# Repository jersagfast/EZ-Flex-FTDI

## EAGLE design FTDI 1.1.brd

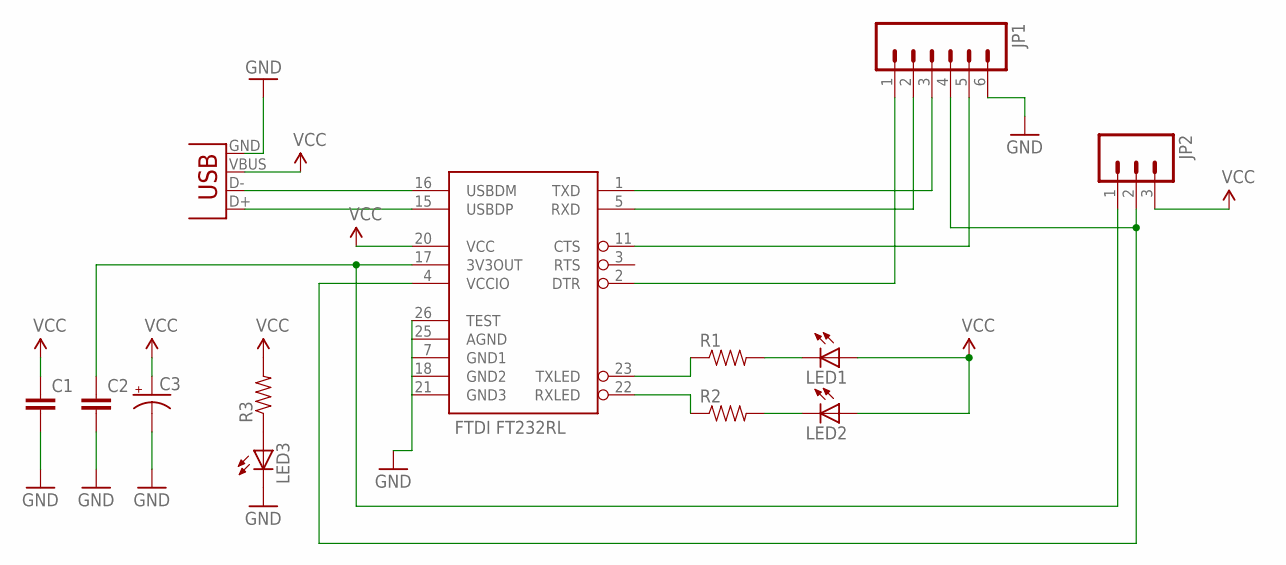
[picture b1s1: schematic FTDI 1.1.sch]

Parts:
C1, C2: CAP0603-CAP; 0603-CAP
C3: CAP_POL1206; EIA3216
JP1: M06SIP; 1X06
JP2: M03PTH; 1X03
LED1, LED2, LED3: LED0603; LED-0603
R1, R2, R3: RESISTOR0603-RES; 0603-RES
U1: FT232RL-BASICSSOP; SSOP28DB
X1: USB-SMD-NS; USB-MINIB-NOSTOP

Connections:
GND: C1.2, C2.2, C3.C (-), JP1.6, LED3.C, U1.7 (GND1), U1.18 (GND2), U1.21 (GND3), U1.25 (AGND), U1.26 (TEST), X1.GND
unnamed: U1.16 (USBDM), X1.D-
unnamed: R1.1, U1.23 (TXLED)
unnamed: LED1.C, R1.2
unnamed: LED2.C, R2.2
unnamed: R2.1, U1.22 (RXLED)
unnamed: U1.15 (USBDP), X1.D+
unnamed: JP1.1, U1.2 (DTR)
unnamed: JP1.2, U1.5 (RXD)
unnamed: JP1.3, U1.1 (TXD)
unnamed: JP1.5, U1.11 (CTS)
unnamed: JP1.4, JP2.2, U1.4 (VCCIO)
unnamed: C2.1, JP2.1, U1.17 (3V3OUT)
unnamed: LED3.A, R3.1
VCC: C1.1, C3.A (+), JP2.3, LED1.A, LED2.A, R3.2, U1.20 (VCC), X1.VBUS

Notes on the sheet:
FTDI FT232RL

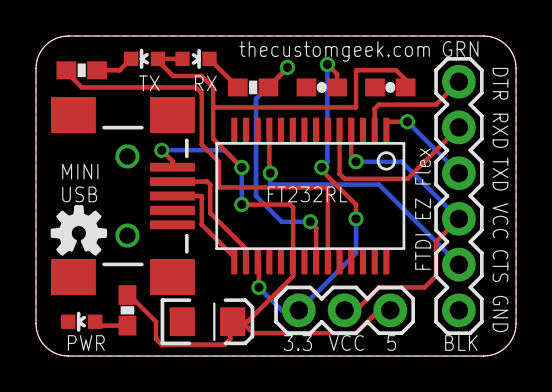
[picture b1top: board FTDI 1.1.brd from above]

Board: 2 copper layers, 26.7 x 17.8 mm, 15 parts (1 on the bottom side), 15 nets.

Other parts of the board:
U$1, U$2: OSHW-LOGO-S

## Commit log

2012-07-13 Fast voltage switching FTDI adapter.
